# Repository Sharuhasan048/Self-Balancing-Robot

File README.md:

# Self-Balancing Robot: Complete Digital Twin & Hardware Implementation

A comprehensive engineering project covering the design, physics simulation, and real-world C++ firmware development of a two-wheeled self-balancing robot using an ESP32.

> **🧭 Repository Navigation & Context**
> This repository is a "Monorepo" containing the entire lifecycle of the robot. 
> - **Just want it to balance?** Head to `firmware/01_Basic_Serial_Tuning` or `03_Final_Cascaded_PID` to upload the working code.
> - **Want to study the control math?** Check out the simulations in the `simulation/` directory.
> - **Curious about failures?** Look into `simulation/Archive_Failed_Models` or `firmware/Experiments_and_Tests` to see what didn't work and why.

## 🚀 Getting Started (Firmware)

If you just built your robot and want to get it standing, jump straight into the `firmware/` directory and use the numbered codes in order:

1. **`01_Basic_Serial_Tuning`**: Start here. The perfect, lightweight code to tune your PID via the Arduino Serial Monitor without complex WiFi setups.
2. **`02_Web_DataLogger`**: Serve a webpage from the ESP32, tune your PID wirelessly, and download live CSV data to analyze your robot's reaction.
3. **`03_Final_Cascaded_PID`**: The ultimate working code. Uses wheel encoders in an outer loop to stop the robot from drifting across the room.
4. **`04_Dual_ESP_Joystick`**: Add a second ESP32 to drive the balanced robot around like an RC car.

*Note: All experimental code (like adaptive PID and unit tests) has been moved to the `firmware/Experiments_and_Tests/` folder so it doesn't clutter your workspace.*

## 💻 Simulation & Digital Twins (MATLAB/Simulink)

We don't just guess PID values. This repository contains high-fidelity Simscape Multibody simulations to test controllers before risking physical hardware.

- **`simulation/Matlab_PID_Tuning/self_bal_3_pid_gui.slx`**: The highly stable, working simulation model used to derive the baseline PID values.
- **`simulation/Matlab_PID_Tuning/self_bal_4.slx`**: An advanced, in-development digital twin incorporating real-world CAD geometries, sensor noise, and a discrete Kalman filter. *(Note: Still undergoing optimization).*
- **`simulation/Archive_Failed_Models/bal_bot2.slx`**: An early simulation iteration that failed due to sensor axis mismatches. Kept for educational and debugging reference.

## 🖨️ Hardware & CAD

- **`hardware/URDF_Model`**: Contains the direct exports from Fusion 360, preserving the exact mechanical geometry, mass distribution, and inertial matrices used by the Simscape simulation and future ROS integrations.

## 📚 Engineering Lessons Learned
For those interested in control theory, this project evolved through several stages:
1. **Initial Balancing:** Classic single-loop PID.
2. **Adaptive PID Experiment:** Attempted a Gain Scheduler based on tilt zones (failed to provide smoothness).
3. **LQR / LQI Experiments:** Attempted modern state-space control (LQI), highlighting the difficulty of tuning LQR without a perfect mathematical model.
4. **Cascaded PID:** The final breakthrough, adding an outer 50Hz position loop to eliminate drift.

Check the `docs/` folder for detailed write-ups on the specific engineering challenges (like Derivative Kick and Integral Windup)!

## License
MIT License.

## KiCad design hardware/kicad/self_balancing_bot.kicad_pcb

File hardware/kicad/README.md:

# KiCad PCB Design — Self-Balancing Robot

Branch: `pcb-design`  
Firmware reference: `firmware/01_Basic_Serial_Tuning/Self_PID_Dir_deg_serial/Self_PID_Dir_deg_serial.ino` (with encoder pins from `Bot_ESP.ino` / `Auto_PID_Tuning.ino`)

## Circuit Diagram

```text
+---------------------------------------------------------------------------------------------------+
|                           3S Li-Ion Battery Pack (11.1V nom / 12.6V max)                        |
+---------------------------------------------------------------------------------------------------+
      | (+) VBAT_RAW                                                                 | (-) GND
      v                                                                              v
+---------------------------------------------------------------------------------------------------+
| Reverse-Polarity Protection: Q1 (IRF9540N P-MOSFET, TO-220)                                       |
|  - Drain (Pin 2) -> VBAT_PROT / VMOTOR rail                                                       |
|  - Source (Pin 3) -> VBAT_RAW (from 3S +)                                                         |
|  - Gate (Pin 1)   -> Pull-down / Zener clamp to GND (turns ON when VBAT_RAW is positive)        |
+---------------------------------------------------------------------------------------------------+
      | VMOTOR                                                                         | GND
      +----------------------------------------+                                     |
      |                                        |                                     |
      v                                        v                                     |
+-----------------------------+      +----------------------------------------------+      |
| TB6612FNG Motor Driver      |      | 5V Linear Regulator Stage (U4: LM7805 TO-220)|      |
| (Socketed on Female Header) |      |  - C_IN_7805 (100uF) across VMOTOR <-> GND   |      |
|  - VM      <-- VMOTOR       |      |  - Pin 1 (IN)  <-- VMOTOR                    |      |
|  - VCC     <-- +3V3 (or +5V)|      |  - Pin 2 (GND) <-- GND                       |      |
|  - GND     <-- GND          |      |  - Pin 3 (OUT) --> +5V rail                  |      |
|  - PWMA    <-- GPIO14       |      |  - C_OUT_7805 (100uF) across +5V <-> GND    |      |
|  - AIN1    <-- GPIO26       |      +----------------------------------------------+      |
|  - AIN2    <-- GPIO25       |                 | +5V                                       |
|  - PWMB    <-- GPIO13       |                 v                                           |
|  - BIN1    <-- GPIO27       |      +----------------------------------------------+      |
|  - BIN2    <-- GPIO19       |      | DOIT ESP32 DevKit V1 (30-Pin, ~28mm wide)  |      |
|  - STBY    <-- GPIO15       |      | (Socketed on 2x15 Female Headers)            |      |
|  - AO1     --> Motor A Pin 1|      |  - VIN / 5V <-- +5V (from LM7805)            |      |
|  - AO2     --> Motor A Pin 2|      |  - 3V3      --> +3V3 logic rail (IMU/Enc/PU) |      |
|  - BO1     --> Motor B Pin 1|      |  - GND      <-- GND                          |<-----+
|  - BO2     --> Motor B Pin 2|      |  - GPIO22   <--> SDA (MPU6050)               |
+-----------------------------+      |  - GPIO23   ---> SCL (MPU6050)               |
                                     |  - GPIO14   ---> PWMA (TB6612FNG)            |
+-----------------------------+      |  - GPIO26   ---> AIN1 (TB6612FNG)            |
| GY-521 MPU6050 (PCB Center) |      |  - GPIO25   ---> AIN2 (TB6612FNG)            |
| (Socketed on Female Header) |      |  - GPIO13   ---> PWMB (TB6612FNG)            |
|  - VCC     <-- +3V3         |      |  - GPIO27   ---> BIN1 (TB6612FNG)            |
|  - GND     <-- GND          |      |  - GPIO19   ---> BIN2 (TB6612FNG)            |
|  - SDA     <--> GPIO22      |      |  - GPIO15   ---> STBY (TB6612FNG)            |
|  - SCL     <-- GPIO23       |      |  - GPIO18   <--- ENC_L_A (Motor A Pin 5)     |
+-----------------------------+      |  - GPIO5    <--- ENC_L_B (Motor A Pin 6)     |
                                     |  - GPIO33   <--- ENC_R_A (Motor B Pin 5)     |
+-----------------------------+      |  - GPIO32   <--- ENC_R_B (Motor B Pin 6)     |
| Start Button + RC Debounce  |      |  - GPIO4    <--- Debounced Button Node       |
|  - R_PU (10k) : +3V3 -> RAW |      +----------------------------------------------+
|  - J_BTN Pin 1: RAW -> GND  |
|    (when button pressed)    |
|  - R_SER (1k) : RAW -> GPIO4|
|  - C_DEB(100nF): GPIO4->GND |
+-----------------------------+

+---------------------------------------------------------------------------------------------------+
| 6-Pin RMC Motor Connectors (Left = Motor A, Right = Motor B)                                      |
|  Pin 1: M+ (AO1 / BO1)   | Pin 2: M- (AO2 / BO2)   | Pin 3: GND                                    |
|  Pin 4: +3V3 (Enc VCC)   | Pin 5: ENC_A (18 / 33)  | Pin 6: ENC_B (5 / 32)                           |
+---------------------------------------------------------------------------------------------------+
```

## Board Summary (`70 mm × 70 mm` Compact THT Socketed Design)

* **Board Size & Mounting:** Compact `70 mm × 70 mm` outline (`Edge.Cuts`) with four `M3` mounting holes (`H1`–`H4`, `4 mm` inset).
* **100% Through-Hole (THT) Socketed Modules:** All pluggable modules use 2.54 mm female headers (`PinSocket`) so they can be unplugged cleanly:
  * **30-Pin DOIT ESP32 DevKit V1 (`J_ESP_L` & `J_ESP_R`):** Dual 15-pin 2.54 mm female headers (~28 mm DevKit width, 22.86 mm / 0.9 in standard row spacing); USB port remains on the DevKit.
  * **GY-521 MPU6050 (`J_MPU6050`):** 8-pin 2.54 mm female header centered at `(35 mm, 35 mm)` on the `70 × 70 mm` board (`SDA = GPIO22`, `SCL = GPIO23`).
  * **TB6612FNG Driver (`J_DRV_L` & `J_DRV_R`):** Dual 8-pin 2.54 mm female headers (`PWMA = 14`, `AIN1 = 26`, `AIN2 = 25`, `PWMB = 13`, `BIN1 = 27`, `BIN2 = 19`, `STBY = 15`).
* **6-Pin RMC Motor Headers (`J_MOTA_6P_RMC` & `J_MOTB_6P_RMC`):** Two 6-pin 2.54 mm headers (`1: M+`, `2: M-`, `3: GND`, `4: +3V3`, `5: ENC_A`, `6: ENC_B`), with encoders mapped to `ENC_L_A = 18`, `ENC_L_B = 5`, `ENC_R_A = 33`, `ENC_R_B = 32`.
* **3S Li-Ion Power & Protection:** `J_BAT` -> `Q1` (`IRF9540N` TO-220 reverse-polarity protection) -> `VMOTOR` + `U4` (`LM7805` TO-220 5V linear regulator with `C_IN_7805` and `C_OUT_7805`) -> ESP32 `VIN/+5V`.
* **Start Button (`GPIO4`) Hardware Debounce:** `J_BTN` + `R_PU` (`10 kΩ`) + `R_SER` (`1 kΩ`) + `C_DEB` (`100 nF` THT disc cap to `GND`) to suppress button bounce/jerk noise.

## Repository Structure

```text
hardware/
└── kicad/
    ├── README.md
    ├── .gitignore
    ├── self_balancing_bot.kicad_pro
    ├── self_balancing_bot.kicad_sch
    └── self_balancing_bot.kicad_pcb
```

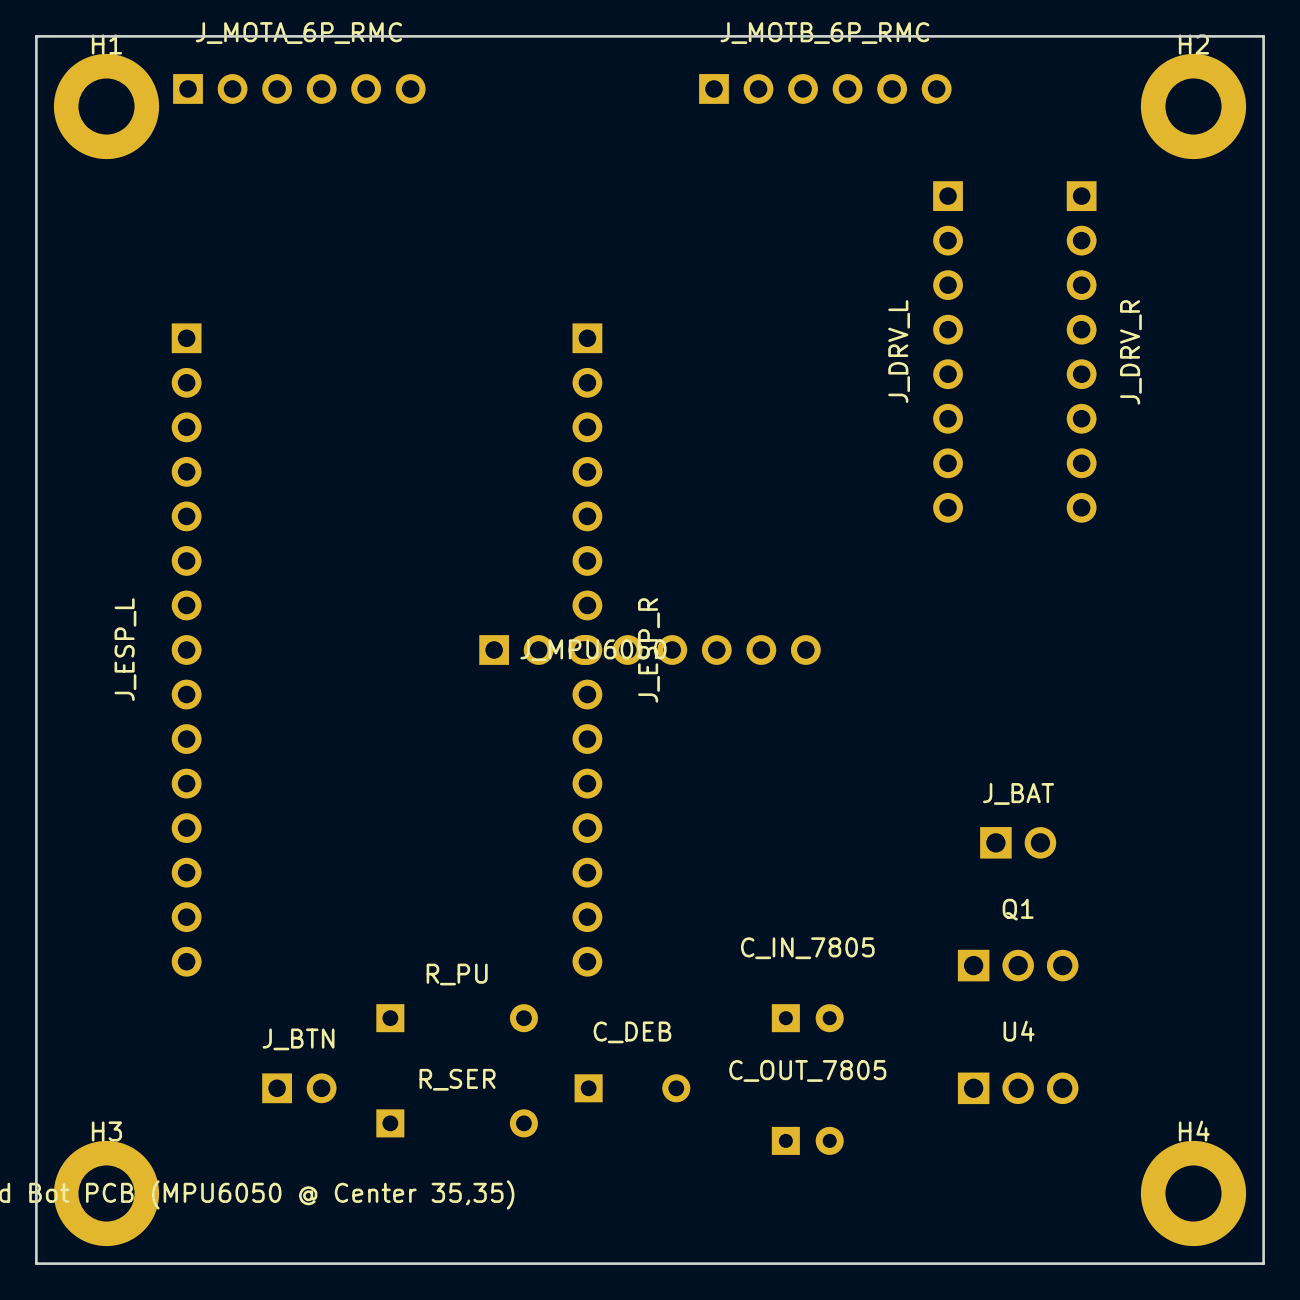
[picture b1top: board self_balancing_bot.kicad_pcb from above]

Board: 2 copper layers, 70.0 x 70.0 mm, 20 parts (0 on the bottom side), 24 nets, no tracks yet.

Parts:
C_DEB: 100nF_THT; C_Disc_D5.0mm_W2.5mm_P5.00mm
C_IN_7805: 100uF_25V; C_Radial_D6.3mm_H11.0mm_P2.50mm
C_OUT_7805: 100uF_16V; C_Radial_D6.3mm_H11.0mm_P2.50mm
H1, H2, H3, H4: M3; MountingHole_3.2mm_M3
J_BAT: 3S_LiIon_In; PinHeader_1x02_P2.54mm_Vertical
J_BTN: Start_Btn_GPIO4; PinHeader_1x02_P2.54mm_Vertical
J_DRV_L: TB6612FNG_L; PinSocket_1x08_P2.54mm_Vertical
J_DRV_R: TB6612FNG_R; PinSocket_1x08_P2.54mm_Vertical
J_ESP_L: ESP32_L_30Pin_Socket; PinSocket_1x15_P2.54mm_Vertical
J_ESP_R: ESP32_R_30Pin_Socket; PinSocket_1x15_P2.54mm_Vertical
J_MOTA_6P_RMC: RMC_6P_Motor_A; PinHeader_1x06_P2.54mm_Vertical
J_MOTB_6P_RMC: RMC_6P_Motor_B; PinHeader_1x06_P2.54mm_Vertical
J_MPU6050: GY521_MPU6050_Center; PinSocket_1x08_P2.54mm_Vertical
Q1: IRF9540N_RevProt; TO-220-3_Vertical
R_PU: 10k_PullUp; R_Axial_DIN0207_L6.3mm_D2.5mm_P7.62mm_Horizontal
R_SER: 1k_Debounce; R_Axial_DIN0207_L6.3mm_D2.5mm_P7.62mm_Horizontal
U4: LM7805_5V_THT; TO-220-3_Vertical

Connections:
+3V3: J_DRV_L.2, J_ESP_L.1, J_MOTA_6P_RMC.4, J_MOTB_6P_RMC.4, J_MPU6050.1, R_PU.1
+5V: C_OUT_7805.1, J_ESP_R.1, U4.3
AIN1: J_DRV_R.3, J_ESP_L.10
AIN2: J_DRV_R.2, J_ESP_L.9
BIN1: J_DRV_R.5, J_ESP_L.11
BIN2: J_DRV_R.6, J_ESP_R.8
ENC_L_A: J_ESP_R.9, J_MOTA_6P_RMC.5
ENC_L_B: J_ESP_R.10, J_MOTA_6P_RMC.6
ENC_R_A: J_ESP_L.7, J_MOTB_6P_RMC.5
ENC_R_B: J_ESP_L.8, J_MOTB_6P_RMC.6
GND: C_DEB.2, C_IN_7805.2, C_OUT_7805.2, J_BAT.2, J_BTN.2, J_DRV_L.3, J_DRV_L.8, J_DRV_R.8, J_ESP_L.14, J_ESP_R.2, J_MOTA_6P_RMC.3, J_MOTB_6P_RMC.3, J_MPU6050.2, J_MPU6050.7, Q1.1, U4.2
MOT_A1: J_DRV_L.4, J_MOTA_6P_RMC.1
MOT_A2: J_DRV_L.5, J_MOTA_6P_RMC.2
MOT_B1: J_DRV_L.7, J_MOTB_6P_RMC.1
MOT_B2: J_DRV_L.6, J_MOTB_6P_RMC.2
PWMA: J_DRV_R.1, J_ESP_L.12
PWMB: J_DRV_R.7, J_ESP_L.15
SCL: J_ESP_R.3, J_MPU6050.3
SDA: J_ESP_R.4, J_MPU6050.4
START_BTN: C_DEB.1, J_ESP_R.13, R_SER.2
START_BTN_RAW: J_BTN.1, R_PU.2, R_SER.1
STBY: J_DRV_R.4, J_ESP_R.15
VBAT_RAW: J_BAT.1, Q1.3
VMOTOR: C_IN_7805.1, J_DRV_L.1, U4.1

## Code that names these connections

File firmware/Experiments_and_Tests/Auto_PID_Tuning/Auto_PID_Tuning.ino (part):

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const int START_BUTTON = 4;

// Motor A (Left)
const int PWMA = 14;
const int AIN1 = 26;
const int AIN2 = 25;

// Motor B (Right)
const int PWMB = 13;
const int BIN1 = 27;
const int BIN2 = 19;

// Encoders
const int ENC_L_A = 18;
const int ENC_L_B = 5;
const int ENC_R_A = 33;
const int ENC_R_B = 32;

// I2C
const int SDA_PIN = 22;
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
    pinMode(START_BUTTON, INPUT_PULLUP);

    pinMode(PWMA, OUTPUT); pinMode(AIN1, OUTPUT); pinMode(AIN2, OUTPUT);
    pinMode(PWMB, OUTPUT); pinMode(BIN1, OUTPUT); pinMode(BIN2, OUTPUT);
    analogWrite(PWMA, 0); analogWrite(PWMB, 0);

    pinMode(ENC_L_A, INPUT_PULLUP); pinMode(ENC_L_B, INPUT_PULLUP);
    pinMode(ENC_R_A, INPUT_PULLUP); pinMode(ENC_R_B, INPUT_PULLUP);
    attachInterrupt(digitalPinToInterrupt(ENC_L_A), isr_encL, RISING);
    attachInterrupt(digitalPinToInterrupt(ENC_R_A), isr_encR, RISING);

    Wire.begin(SDA_PIN, SCL_PIN);
    Wire.setClock(400000UL);
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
